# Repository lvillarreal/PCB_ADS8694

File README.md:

# PCB PARA ADS8694

## Características del PCB

 - 4 entradas diferenciales con acondiconamiento (AD8221)
 - Entrada canal 0 sin filtro RC
 - Entradas canales 1-3 con filtro RC, LP 
 - Salida compatible con Pmod (6x6, 2.54mm, 90º) de Xilinx
 - Uso de referencia interna de AD

## Características ADS8694

 - 18 bits
 - 500 kSPS
 - Filtro Pasa bajos incorporado internamente, fc=15 kHz (Oversampling)
 - Interface SPI
 - Pin de alarma
 - Impedancia de entrada: 1MΩ
 - Encapsulado TSSOP (38)
 - Conversión SAR (aproximaciones sucesivas)

### Diagrama en bloques

### Pines

### Definicion de Pines

| Nº | Nombre | I/O | Descripción |
| -- | -----| --- | ----------- |
| 1  | SDI  |Entrada Digital   | Data in     |
| 2  | /RST-/PD | Entrada Digital  | Reset y Power Down     |
| 3  | DAISY  | Entrada Digital   | Modo Daisy-Chain     |
| 4  | /REFSEL  |Entrada Digital  | Entrada lógica activa por bajo para habilitar la referencia interna. Cuando está en bajo, la referencia interna está habilitada.  REFIO se convierte en una salida que incluye la referencia de tensión V_REF. Cuando REFSEL está en alto la ref interna está deshabilitada y REFIO se convierte en la referencia (entrada analógica)|
| 5  | REFIO  | Entrada/Salida Analógica  | Se explica arriba |
| 6  | REFGND  | Power Supply   | Pin de GND analógica, corto al plano analógico GND. Desacoplar con REFIO en el pin 5 y REFCAP en el pin 7 |
| 7  | REFCAP  | Salida Analógica | Pin de condensador de desacoplamiento de referencia ADC. Desacoplar con REFGND en el pin 6 |
| 8 |  AGND | Power Supply   | Pin de tierra analógica. Desacoplar con AVDD en pin 9 |
| 9  |  AVDD |  Power Supply  | Pin suministro analógico. Desacoplar con AGND pin 8|
| 10 | AUX_IN | Entrada Analógica | Canal de entrada auxiliar: entrada positiva. Desacoplar con pin 11, AUX_GND |
| 11 | AUX_GND | Entrada Analógica | Canal de entrada auxiliar: entrada negativa. Desacoplar con pin 10, AUX_IN |
|16|AIN_0P| Entrada analógica |Canal de entrada analógica 0, entrada positiva. Desacoplar con AIN_0GND en el pin 17|
|17| AIN_0GND| Entrada analógica| Canal de entrada analógica 0, entrada negativa. Desacoplar con AIN_0P en el pin 16|
| 18 | AIN_1P | Entrada analógica |  |
| 19 |AIN_1GND | Entrada analógica |  |
| 20 | AIN_2GND | Entrada analógica |  |
| 21 | AIN_2P | Entrada analógica |  |
| 22 | AIN_3GND | Entrada analógica |  |
| 23 | AIN_3P | Entrada analógica |  |
|28| AGND| Power Supply| Toma de tierra analógica|
|29| AGND| Power Supply| Toma de tierra analógica|
|30| AVDD| Power Supply| Fuente de alimentación analógica. Desacoplar con AGND
|31| AGND| Power Supply| Toma de tierra analógica|
|32| AGND| Power Supply|
|33| DGND | Power Supply | Desacoplar con 35, DVDD|
|34| AVDD | Power Supply | Desacoplar con 34, AGND|
|35|ALARM| Salida Digital |Salida de alarma activa por alto|
|36|SDO| Salida Digital | Dato de salida, SPI|
|37|SCL| Entrada Digital | clock SPI |
|38|/CS| Entrada digital | Chip Slect SPI, activo por bajo|

### Entrada Analógica

El rango de tensión de entrada se puede configurar para ±2.5 Vref, ±1.25 Vref ; ±0.625 Vref (bipolar) o 0 a 2.5 Vref, 0 a 1.25 Vref (unipolar). La configuración es independiente para cada canal (4 canales).
El dispositivo muestrea la diferencia entre AIN_nP y AIN_nGND, donde el valor máximo que puede tomar AIN_nGND es ±0.1 V.

### Programmable Gain Amplifier (PGA)

Dependiendo del rango de la señal de entada, se puede ajustar la ganancia modificando los bits Range_CHn [3:0] en el registro de programa.El valor predeterminado es 0000, que corresponde a un rango de señal de entrada de ± 2.5 × Vref.

| Rango de entrada analógica | Bit 3 | Bit 2 | Bit 1 | Bit 0 |
|----------------------------|-------|-------|-------|-------|
| ±2.5 x Vref                  | 0     | 0     | 0     | 0     |
| ±1.25 x Vref                 | 0     | 0     | 0     | 1     |
| ±0.625 x Vref                | 0     | 0     | 1     | 0     |
|0 a 2.5 x Vref                | 0     | 1     | 0     | 1     |
|0 a 1.25 x Vref               | 0     | 1     | 1     | 0     |

### Multiplexor

Dispone de un mux analógico de 4 canales. Puede funcionar en modo manual o de escaneo automático.En modo manual (MAN_Ch_n), el canal se selecciona para cada muestra a través de un registro de escritura; en modo de escaneo automático (AUTO_RST), el número de canal se incrementa automáticamente en cada flanco descendente de /CS después de muestrear el canal actual.
Las entradas analógicas pueden ser seleccionadas por un scaneo automático configurando los registros pertinente. El dispositivo escanea solo las entradas analógicas seleccionadas en orden ascendente. El rendimiento total es de 500kSPS, pero se divide entre los canales activos. Si hay uno solo activo, será de 500 kSPS; si hay 2 será de 250kSPS por canal; etc.

### Referencia interna
Circuito recomendado

### Modos de funcionamiento
El ADS8694 admite múltiples modos de operación que son programables por software. Después de encendido, el dispositivo se coloca en modo inactivo y no realiza ninguna función hasta que se recibe un comando del usuario. Más adelante se enumeran en una tabla todos los comandos para ingresar a los diferentes modos del dispositivo. Después del encendido, los registros de programa se activan con los valores predeterminados y requieren ajustes de configuración apropiados antes de realizar cualquier conversión. El siguiente diagrama explica cómo cambiar el dispositivo de un modo de operación a otro.

### Valores de LSB para Vref de 4.096 V

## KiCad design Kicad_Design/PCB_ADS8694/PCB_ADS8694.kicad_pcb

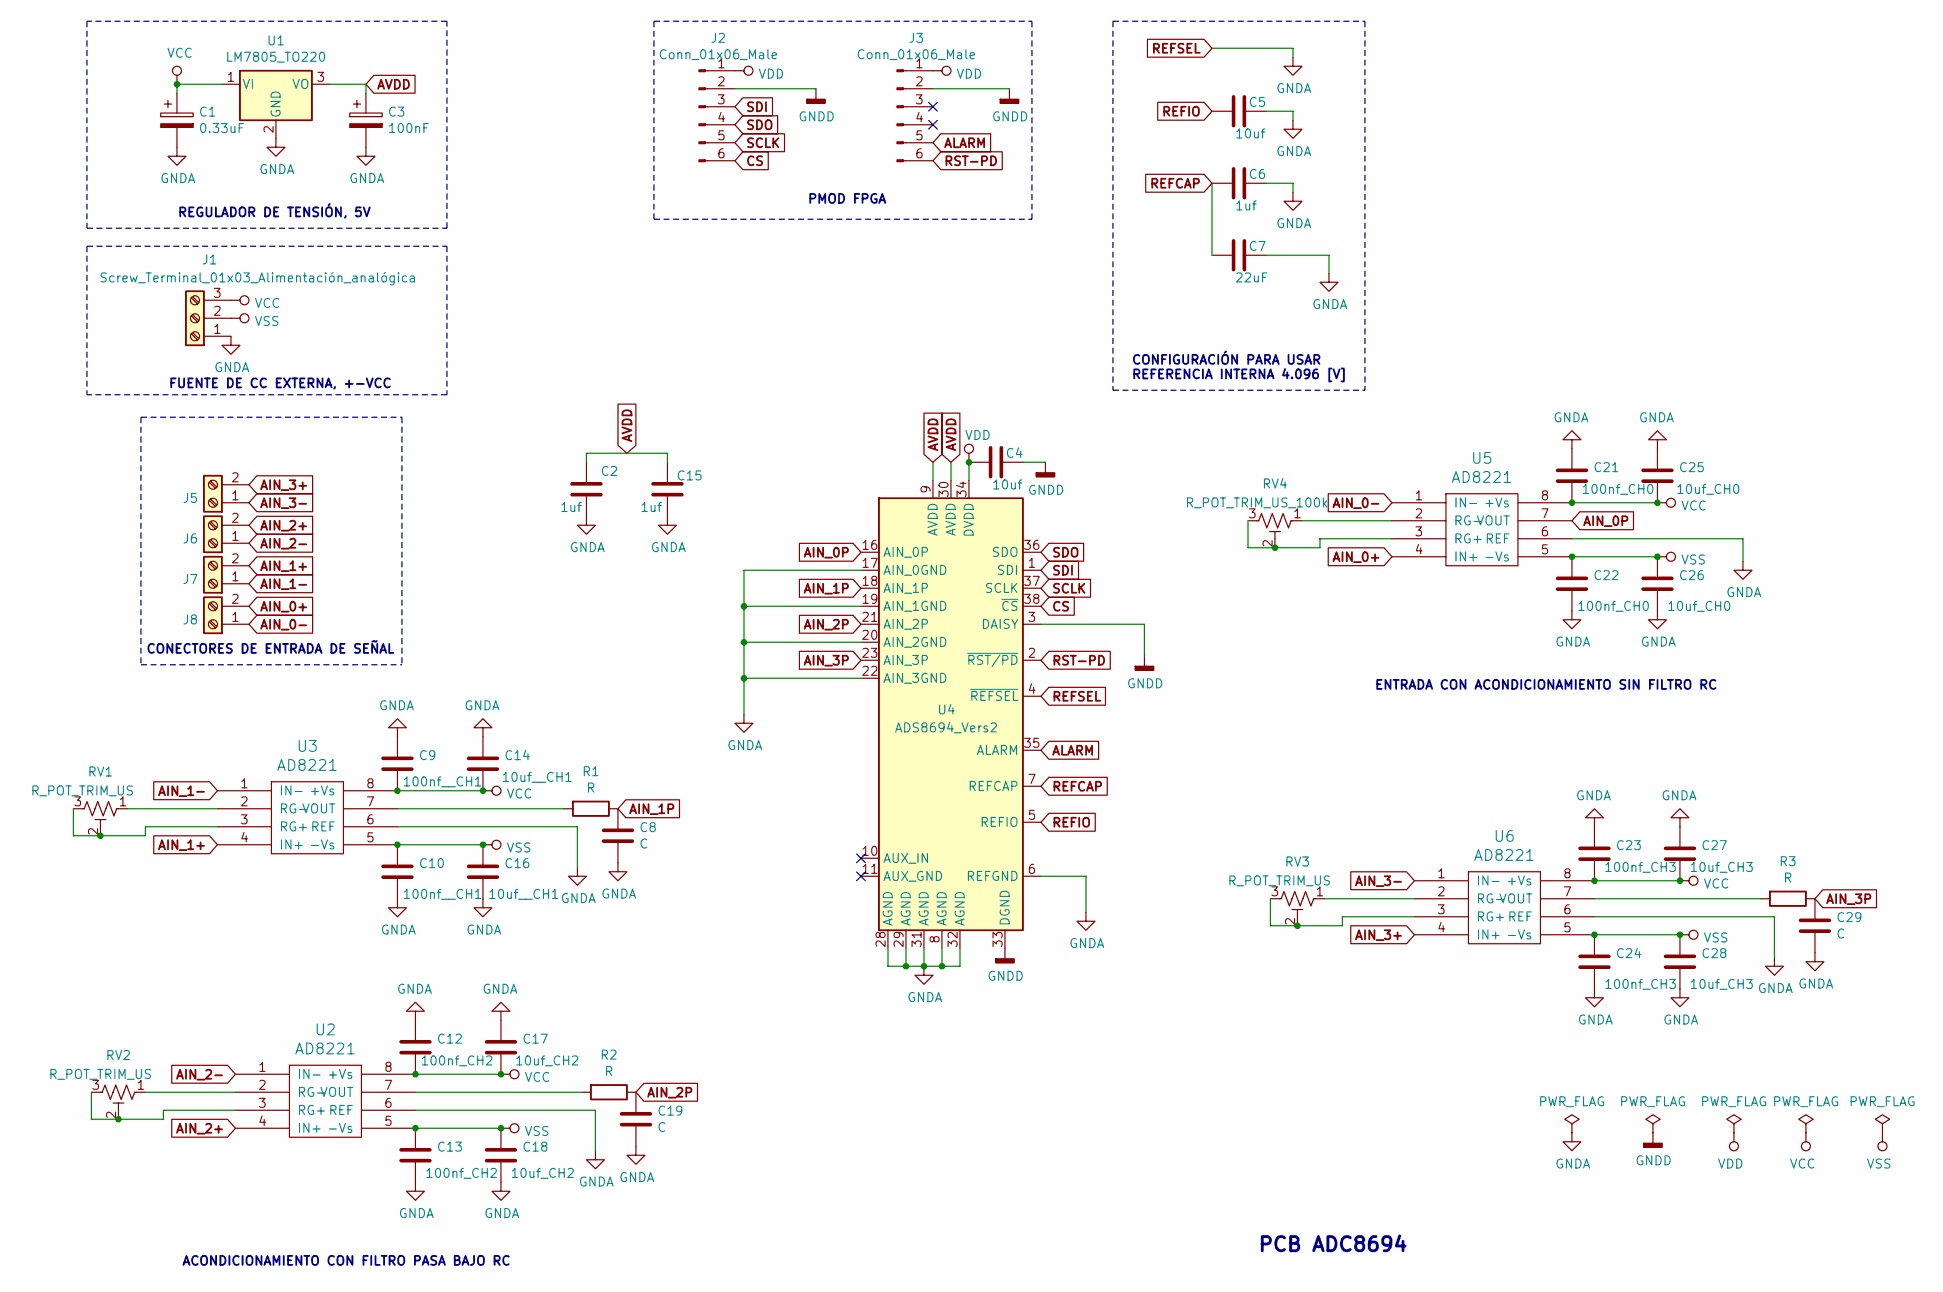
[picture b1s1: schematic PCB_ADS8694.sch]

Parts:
C1: 0.33uF; CP_Radial_D5.0mm_P2.00mm
C2, C6, C15: 1uf; C_0603_1608Metric
C3: 100nF; C_Disc_D5.0mm_W2.5mm_P5.00mm
C4, C5: 10uf; CP_Radial_D5.0mm_P2.00mm
C7: 22uF; CP_Radial_D5.0mm_P2.00mm
C8, C19, C29: C; C_Disc_D5.0mm_W2.5mm_P5.00mm
C9, C10: 100nf__CH1; C_0603_1608Metric
C12, C13: 100nf_CH2; C_0603_1608Metric
C14, C16: 10uf__CH1; CP_Radial_D5.0mm_P2.00mm
C17, C18: 10uf_CH2; CP_Radial_D5.0mm_P2.00mm
C21, C22: 100nf_CH0; C_0603_1608Metric
C23, C24: 100nf_CH3; C_0603_1608Metric
C25, C26: 10uf_CH0; CP_Radial_D5.0mm_P2.00mm
C27, C28: 10uf_CH3; CP_Radial_D5.0mm_P2.00mm
J1: Screw_Terminal_01x03_Alimentación_analógica; TerminalBlock_Altech_AK300-3_P5.00mm
J2, J3: Conn_01x06_Male; PinHeader_1x06_P2.54mm_Vertical
J5: Screw_Terminal_01x02_CH3; TerminalBlock_Altech_AK300-2_P5.00mm
J6: Screw_Terminal_01x02_CH2; TerminalBlock_Altech_AK300-2_P5.00mm
J7: Screw_Terminal_01x02_CH1; TerminalBlock_Altech_AK300-2_P5.00mm
J8: Screw_Terminal_01x02_CH0; TerminalBlock_Altech_AK300-2_P5.00mm
R1, R2, R3: R; R_Axial_DIN0207_L6.3mm_D2.5mm_P10.16mm_Horizontal
RV1, RV2, RV3: R_POT_TRIM_US; Potentiometer_Bourns_3266Y_Vertical
RV4: R_POT_TRIM_US_100k; Potentiometer_Bourns_3266Y_Vertical
U1: LM7805_TO220; TO-220-3_Vertical
U2, U3, U5, U6: AD8221; MSOP-8_3x3mm_P0.65mm
U4: ADS8694_Vers2; TSSOP-38_4.4x9.7mm_P0.5mm

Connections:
AIN_0+: J8.2, U5.4 (IN+)
AIN_0-: J8.1, U5.1 (IN-)
AIN_0P: U4.16 (AIN_0P), U5.7 (VOUT)
AIN_1+: J7.2, U3.4 (IN+)
AIN_1-: J7.1, U3.1 (IN-)
AIN_1P: C8.1, R1.1, U4.18 (AIN_1P)
AIN_2+: J6.2, U2.4 (IN+)
AIN_2-: J6.1, U2.1 (IN-)
AIN_2P: C19.1, R2.1, U4.21 (AIN_2P)
AIN_3+: J5.2, U6.4 (IN+)
AIN_3-: J5.1, U6.1 (IN-)
AIN_3P: C29.1, R3.1, U4.23 (AIN_3P)
ALARM: J3.5, U4.35 (ALARM)
AVDD: C2.1, C3.1, C15.2, U1.3 (VO), U4.9 (AVDD), U4.30 (AVDD)
CS: J2.6, U4.38 (~CS)
GNDD: C4.1, J2.2, J3.2, U4.3 (DAISY), U4.33 (DGND)
unnamed: R1.2, U3.7 (VOUT)
unnamed: R2.2, U2.7 (VOUT)
unnamed: R3.2, U6.7 (VOUT)
unnamed: RV1.1, U3.2 (RG-)
unnamed: RV1.2, RV1.3, U3.3 (RG+)
unnamed: RV2.1, U2.2 (RG-)
unnamed: RV2.2, RV2.3, U2.3 (RG+)
unnamed: RV3.1, U6.2 (RG-)
unnamed: RV3.2, RV3.3, U6.3 (RG+)
unnamed: RV4.1, U5.2 (RG-)
unnamed: RV4.2, RV4.3, U5.3 (RG+)
REFCAP: C6.2, C7.2, U4.7 (REFCAP)
REFIO: C5.2, U4.5 (REFIO)
REFSEL: C1.2, C2.2, C3.2, C5.1, C6.1, C7.1, C8.2, C9.1, C10.2, C12.1, C13.2, C14.1, C15.1, C16.2, C17.1, C18.2, C19.2, C21.1, C22.2, C23.1, C24.2, C25.1, C26.2, C27.1, C28.2, C29.2, J1.1, U1.2 (GND), U2.6 (REF), U3.6 (REF), U4.4 (~REFSEL), U4.6 (REFGND), U4.8 (AGND), U4.17 (AIN_0GND), U4.19 (AIN_1GND), U4.20 (AIN_2GND), U4.22 (AIN_3GND), U4.28 (AGND), U4.29 (AGND), U4.31 (AGND), U4.32 (AGND), U5.6 (REF), U6.6 (REF)
RST-PD: J3.6, U4.2 (~RST/PD)
SCLK: J2.5, U4.37 (SCLK)
SDI: J2.3, U4.1 (SDI)
SDO: J2.4, U4.36 (SDO)
VCC: C1.1, C9.2, C12.2, C14.2, C17.2, C21.2, C23.2, C25.2, C27.2, J1.3, U1.1 (VI), U2.8 (+Vs), U3.8 (+Vs), U5.8 (+Vs), U6.8 (+Vs)
VDD: C4.2, J2.1, J3.1, U4.34 (DVDD)
VSS: C10.1, C13.1, C16.1, C18.1, C22.1, C24.1, C26.1, C28.1, J1.2, U2.5 (-Vs), U3.5 (-Vs), U5.5 (-Vs), U6.5 (-Vs)

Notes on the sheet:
CONFIGURACIÓN PARA USAR REFERENCIA INTERNA 4.096 [V]
PMOD FPGA
REGULADOR DE TENSIÓN, 5V
PCB ADC8694
FUENTE DE CC EXTERNA, +-VCC
ENTRADA CON ACONDICIONAMIENTO SIN FILTRO RC
CONECTORES DE ENTRADA DE SEÑAL
ACONDICIONAMIENTO CON FILTRO PASA BAJO RC

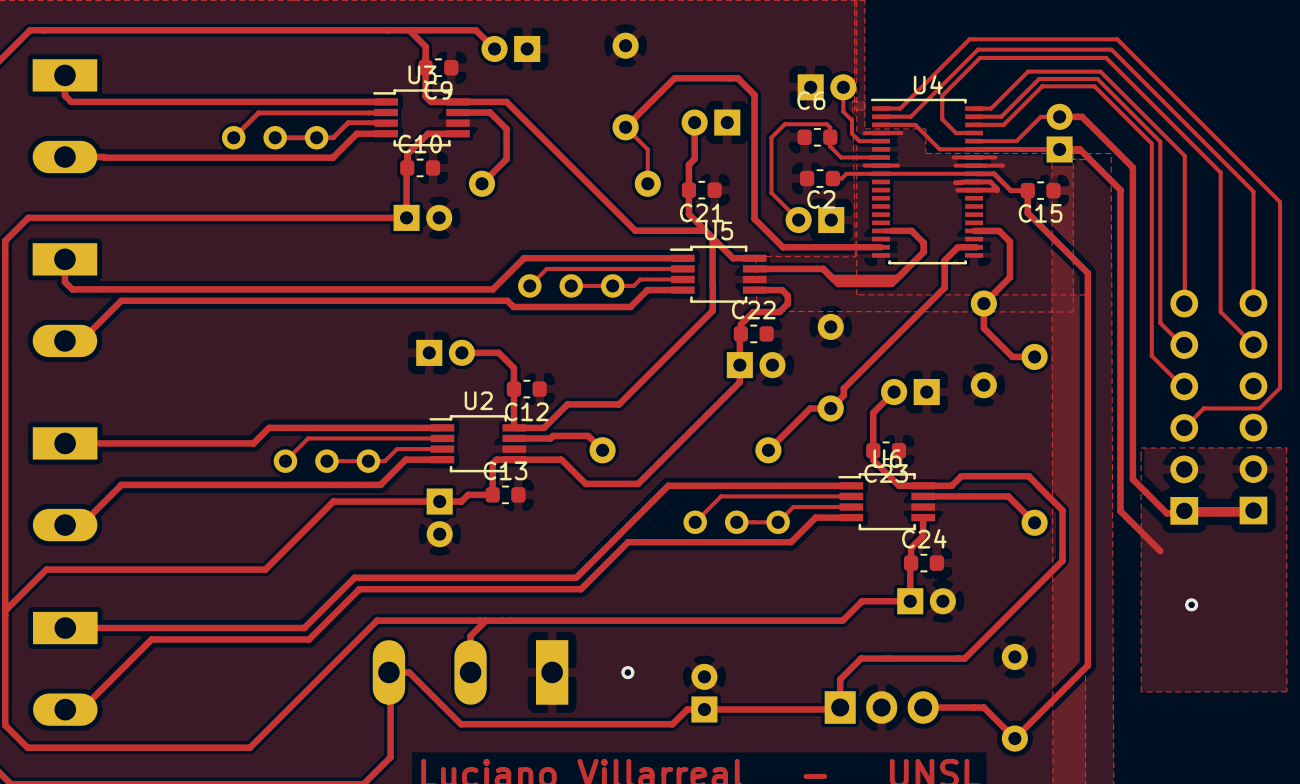
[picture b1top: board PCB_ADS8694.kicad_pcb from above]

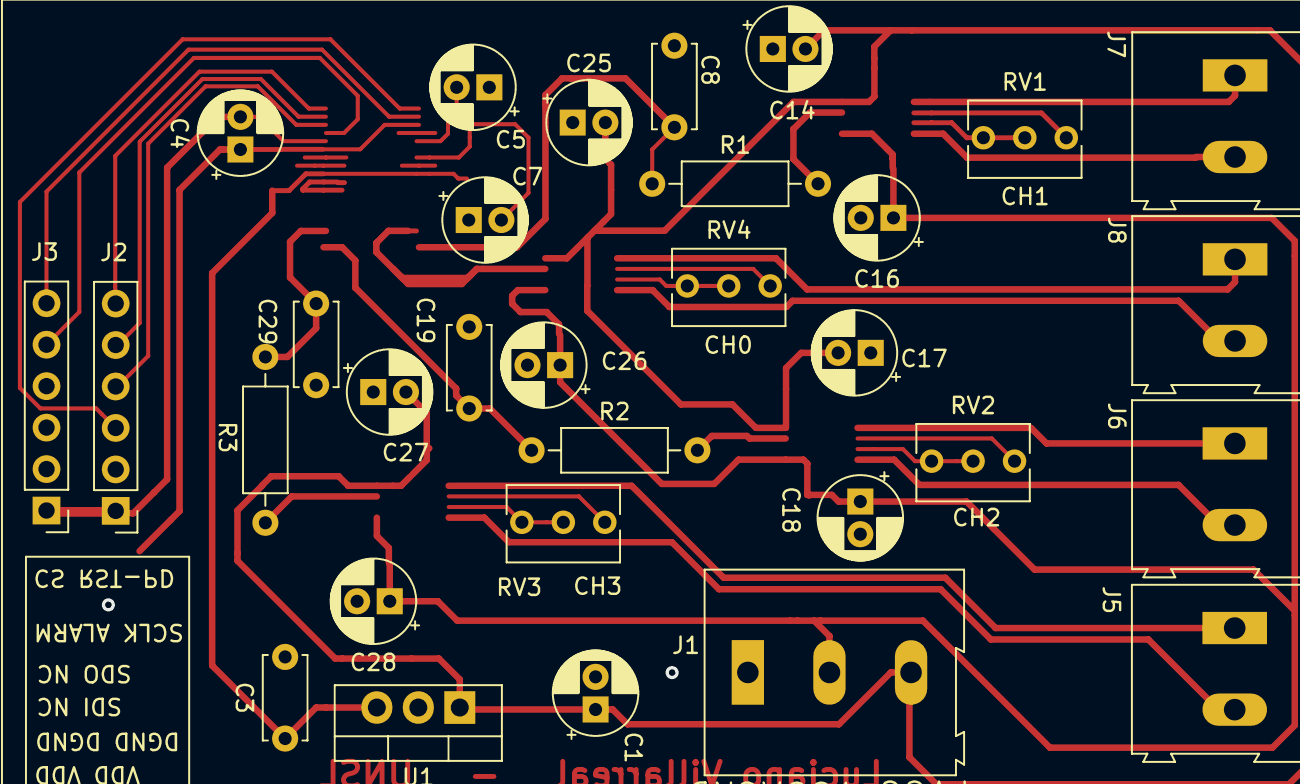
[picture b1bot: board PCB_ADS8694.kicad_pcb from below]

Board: 2 copper layers, 47 parts (31 on the bottom side), 37 nets.

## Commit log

2019-04-30 Se crea simbolo de ADS8694
2019-05-02 Edición de readme.m
2019-05-02 Se crea circuito ded referencia interna, pmod y circuito de tension de alimentación analógica
2019-05-03 Se agrega circuito de seleccion modo daisy-chain
2019-05-07 Agregado de info en README
2019-05-07 Se agrega acondicionamiento, entradas analogicas, cambios varios
2019-05-08 modificacion
2019-05-08 Se agregan AD8221 en los 4 canales
2019-05-11 modificacion readme
2019-05-11 Se agrega AD8221 en 4 canales, se agrega pin para daisy chain
2019-05-11 Se agrega informacion, primer version terminada
2019-05-12 cambios de alimentación
2019-05-13 Agregado de capacitor para filtrar componente de CC en canal 0
2019-05-13 Asignacion de huellas
2019-05-14 agregado de capacitores de desacoplo
2019-05-15 Agregado de capacitores de desacople, cambios en simbolo de AD
2019-05-15 Creacion de listado de redes
2019-05-15 Modificacion simbolo AD, agregado de capacitores de desacople, asignacion de huellas
2019-05-18 se elimina canal aux, se elimina jumper daisy
2019-05-18 PCB creado, V1
2019-05-18 lista de redes
2019-05-19 Cambios en encapsulados. Agregado de serigrafía
2019-05-19 cambios varios, reduccion de tamaño
2019-05-19 Cambio en ancho de pistas
2019-05-19 Agregado de cotas
2019-05-19 Máscaras
2019-05-20 PCB V1
2019-05-24 Se cambia orientacion de bornera +-12V, con esto se evita usar vias para unir plano agnd. Se agregan vias para unir agnd con dgnd
2019-05-24 Se agranda el ancho de pista canal 0, para efectauar mediciones con mayor facilidad
2019-05-24 union agnd dgnd
2019-06-01 PCV V1
2019-06-02 Cambios en conector pmod
2019-06-03 Capacitores 10uF de smd a THT
2019-06-07 Cambios varios, Version 1 funcional
2019-06-10 Capa de cobre invertida
2019-06-10 Se agrega dcp01b
2019-06-10 Se agrega DCP01B, alimentado por lm7805. LA alimentacion de la placa debe ser mayor a 7V
2019-08-21 version finalizada
